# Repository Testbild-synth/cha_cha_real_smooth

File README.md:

# 4HP version of Voxmachina ChaCha VCLFO Eurorack module

This project is a 4HP fork of the Voxmachina chacha VCLFO eurorack module.

## Status: Confirmed working!

## Hardware and PCB

I had it in my head to do this in 4hp, but it was quite a pain.
In the end i had to fit a lot of standing resistors which I usually dislike but i think
I spaced them in a way that wasn't too confusing.

You can simply order the pcbs as-is on any pcb manufacturing site, 
I use jlcpcb. You can order all the pcbs with the standard settings.If for some reason the dimensions for the front panel
are not entered (happens to me sometimes on jlc), put them as 128.5x20mm.

The build is relatively straight forward, apart from the standing resistors which are kind of annoying.

schematic and bom are split between the two boards, as that's how voxmachina had his project set up. So just order components from both bom files

# Tuning
I simplified the sin shaping circuit so there is only one trimmer (for the saw shaper).
As for how to tune it, check out [voxmachina's videos on the module on youtube](https://www.youtube.com/watch?v=DsVzbcYWhuM&t=31s).

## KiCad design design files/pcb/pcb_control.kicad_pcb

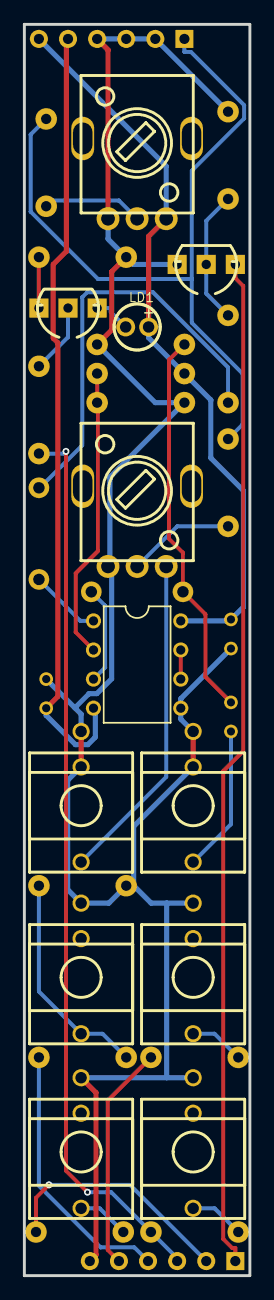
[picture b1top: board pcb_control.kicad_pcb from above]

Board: 2 copper layers, 19.7 x 109.2 mm, 33 parts (0 on the bottom side), 27 nets.

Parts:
C6, C7, C12: 0.1uf; RAD-0.1
CV1: CVIN; THONKICONN
CV2: RESET; THONKICONN
D1, D5: 1N4148; DO-35_BD2.0-L4.0-P8.00-D0.5-FD
H1: TOP_H; HDR-F-2.54_1X6
H2: BOT_H; HDR-F-2.54_1X6
IC1: TL072; DIL08
LD1: CLOCK; LED-TH_BD4.1-P2.00-D0.5-RD_RED
OUT1: SINE; THONKICONN
OUT2: TRI; THONKICONN
OUT3: SQR; THONKICONN
OUT4: SAWUP; THONKICONN
Q1, Q3: BC550; BC547
R1: 4.7k; AXIAL-0.3EZ
R2: 330k; AXIAL-0.3EZ
R3, R11: B100k; R09-5KΩ
R4, R8, R10, R14: 100k; AXIAL-0.3EZ
R5: 47k; AXIAL-0.3EZ
R7, R19, R20, R30, R41: 1k; AXIAL-0.3EZ
R17: 3.3k; AXIAL-0.3EZ
R21: 10k; AXIAL-0.3EZ

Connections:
+12V: C7.2, H1.6, IC1.8, LD1.2, R2.1, R3.3
-12V: C6.1, H1.5, IC1.4
AGND: C6.2, C7.1, CV1.1, CV1.2, CV2.1, CV2.2, H1.2, H1.3, H1.4, H2.6, IC1.5, OUT1.1, OUT2.1, OUT3.1, OUT4.1, Q1.3, R1.1, R3.1, R5.2, R11.1, R14.1, R19.1, R20.1
C12_2: C12.2, D5.1, R1.2
CV1_3: CV1.3, R11.3
CV2_3: C12.1, CV2.3
CVIN: H1.1, R4.2, R8.2
D5_2: D5.2, IC1.3
IC1_1: D1.1, IC1.1
IC1_2: IC1.2, R2.2, R5.1
IC1_6: IC1.6, IC1.7
Q3_1: LD1.1, Q3.1
Q3_2: Q3.2, R21.2
R4_1: R3.2, R4.1
R7_2: OUT2.3, R7.2
R8_1: R8.1, R11.2
R14_2: OUT3.3, R10.2, R14.2
R17_1: D1.2, R17.1
R17_2: Q1.2, R17.2, R19.2
R20_2: Q3.3, R20.2
R30_1: OUT1.3, R30.1
R41_2: OUT4.3, R41.2
RESETIN: H2.1, Q1.1
SAW: H2.5, R41.1
SINE: H2.2, R30.2
SQR: H2.4, R10.1
TRI: H2.3, R7.1, R21.1

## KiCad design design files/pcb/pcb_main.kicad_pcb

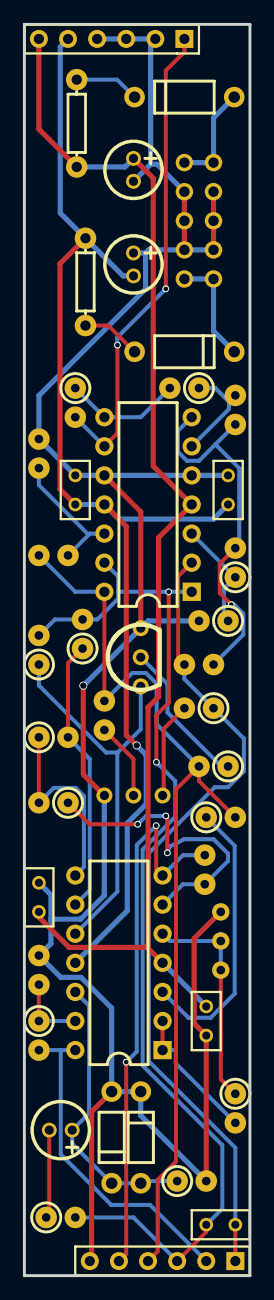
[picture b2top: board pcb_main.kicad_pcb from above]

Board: 2 copper layers, 19.7 x 109.2 mm, 44 parts (0 on the bottom side), 31 nets.

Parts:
C1, C4, C8: 10uF; CAP-TH_BD5.0-P2.00-D0.8-FD
C2, C3, C6, C7, C10: 0.1uf; RAD-0.1
D1, D2: 1N4148; DO-35_BD2.0-L4.0-P8.00-D0.5-FD
D3, D4: 1N5819; DO-41_BD2.4-L4.7-P8.70-D0.9-RD
H1: TOP_H; HDR-F-2.54_1X6
H2: BOT_H; HDR-F-2.54_1X6
P1: POWER; EURORACK SHROUDED POWER 10 PIN
Q1, Q2: BC550; TO92-X
R1: 1k; RESISTOR-VERTICAL
R2, R14, R16, R20: 10k; RESISTOR-VERTICAL
R3: 39k; RESISTOR-VERTICAL
R4, R6, R7, R8, R15, R17, R19, R22: 100k; RESISTOR-VERTICAL
R5: 22k; RESISTOR-VERTICAL
R9, R10, R11, R12, R13: 47k; RESISTOR-VERTICAL
R18: 20k; RESISTOR-VERTICAL
R21: 51k; RESISTOR-VERTICAL
R23, R24: 10; AXIAL-0.3
TM1: 20k; TRIMPOT
U1, U2: TL074; DIP-14

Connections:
+12V: C3.2, C4.1, C6.2, H1.6, R23.2, U1.4, U2.4
-12V: C7.1, C8.2, C10.1, H1.5, R24.2, U1.11, U2.11
CVIN: H1.1, R4.1, U2.9
D3_1: D3.1, R23.1
D4_2: D4.2, R24.1
GND: C3.1, C4.2, C6.1, C7.2, C8.1, C10.2, D1.1, D2.2, H1.2, H1.3, H1.4, H2.6, P1.2, P1.3, P1.4, Q1.3, Q2.3, R1.2, R5.1, R10.1, R11.1, TM1.1, U2.5, U2.10
P1_1: D3.2, P1.1
P1_5: D4.1, P1.5
Q1_1: Q1.1, R12.1
Q2_2: Q2.2, R20.2
R3_2: C1.2, R3.2
R6_1: R6.1, R7.2, U2.6
R7_1: R4.2, R7.1, U2.8
R9_1: R6.2, R8.1, R9.1, U2.7
R10_2: R10.2, R13.1, U2.12
R11_2: R9.2, R11.2, U2.3
R14_1: Q1.2, R14.1
R15_2: R15.2, R18.1, U1.8
R17_2: R15.1, R17.2, U1.9
R19_2: Q2.1, R19.2, U1.10
R21_1: R21.1, U1.1, U1.2
R22_2: R22.2, U1.3
RESETIN: C2.2, H2.1, R8.2, R12.2, U2.2
SAW: H2.5, R16.2, U1.7
SINE: H2.2, R2.1, U1.14
SQR: H2.4, R13.2, R14.2, R20.1, R22.1, U2.14
TRI: C2.1, H2.3, R3.1, R17.1, R19.1, U2.1, U2.13
U1_5: R21.2, TM1.2, TM1.3, U1.5
U1_6: R16.1, R18.2, U1.6
U1_12: C1.1, D1.2, D2.1, R5.2, U1.12
U1_13: R1.1, R2.2, U1.13

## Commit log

2022-10-04 upload
2022-11-02 Updated main pcb
2022-11-02 added annotations to pcbs
